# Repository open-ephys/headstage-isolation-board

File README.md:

# headstage-isolation-board

## this design is not functional right now, see below

isolation board for RHD headstge, electrically decouples headstage from aq. board.
This could be useful for mitigating recording noise in some scenarious, or simplify proper grounding practive, especially if multiple recording rigs share the same acquisition board. Eventually, this device could be used to provide safety for human EEG or intracortical applications, but this would require extensive testing and approval procedures.

*This device has not been tested and is not considered safe for any use case. Only use this if you are approved to do so independently.*

# operating principle
This isolation board translates the LVDS signals to a single ended CMOS signal, isolates this signal and translates it back to LVDS. Power isolation is accomplished through a separate 5V isolation transformer.

## 2do:
change this to use the basic design form the FMC card at 
https://github.com/open-ephys/next-gen-system/tree/master/FMC-board

use only IEC60601-1 certified parts, this way we're on the safe side for US and EU standards
http://www.cui.com/catalog/resource/iec-60601-1-medical-design-standards.pdf

power DC-DC: http://www.digikey.com/en/product-highlight/r/recom-power/dcdc-converters
cmos isolation: http://www.analog.com/media/en/technical-documentation/data-sheets/ADuM4400_4401_4402.pdf

# old spec below

Based on Analog Devices ADUM3440 isolators 9 http://www.analog.com/media/en/technical-documentation/data-sheets/ADuM3440_3441_3442.pdf )
UL recognition: 2500 V rms for 1 minute per UL 1577,  CSA Component Acceptance Notice #5A, VDE certificate of conformity, DIN V VDE V 0884-10 (VDE V 0884-10):2006-12 
V_IORM = 560 V peak

LVDS<-> CMOS trsnalation is done via on Analog Devices ADN4664 Dual, 3 V, CMOS, LVDS Differential Line Receivers ( http://www.analog.com/media/en/technical-documentation/data-sheets/ADN4664.pdf ) and ADN4663 Dual, 3 V, CMOS, LVDS High Speed Differential Drivers ( http://www.analog.com/media/en/technical-documentation/data-sheets/ADN4663.pdf )

Power isolation is done with a Murata NMV0505 3kVDC Isolated 5V DC/DC Converters ( http://power.murata.com/data/power/ncl/kdc_nmv.pdf )

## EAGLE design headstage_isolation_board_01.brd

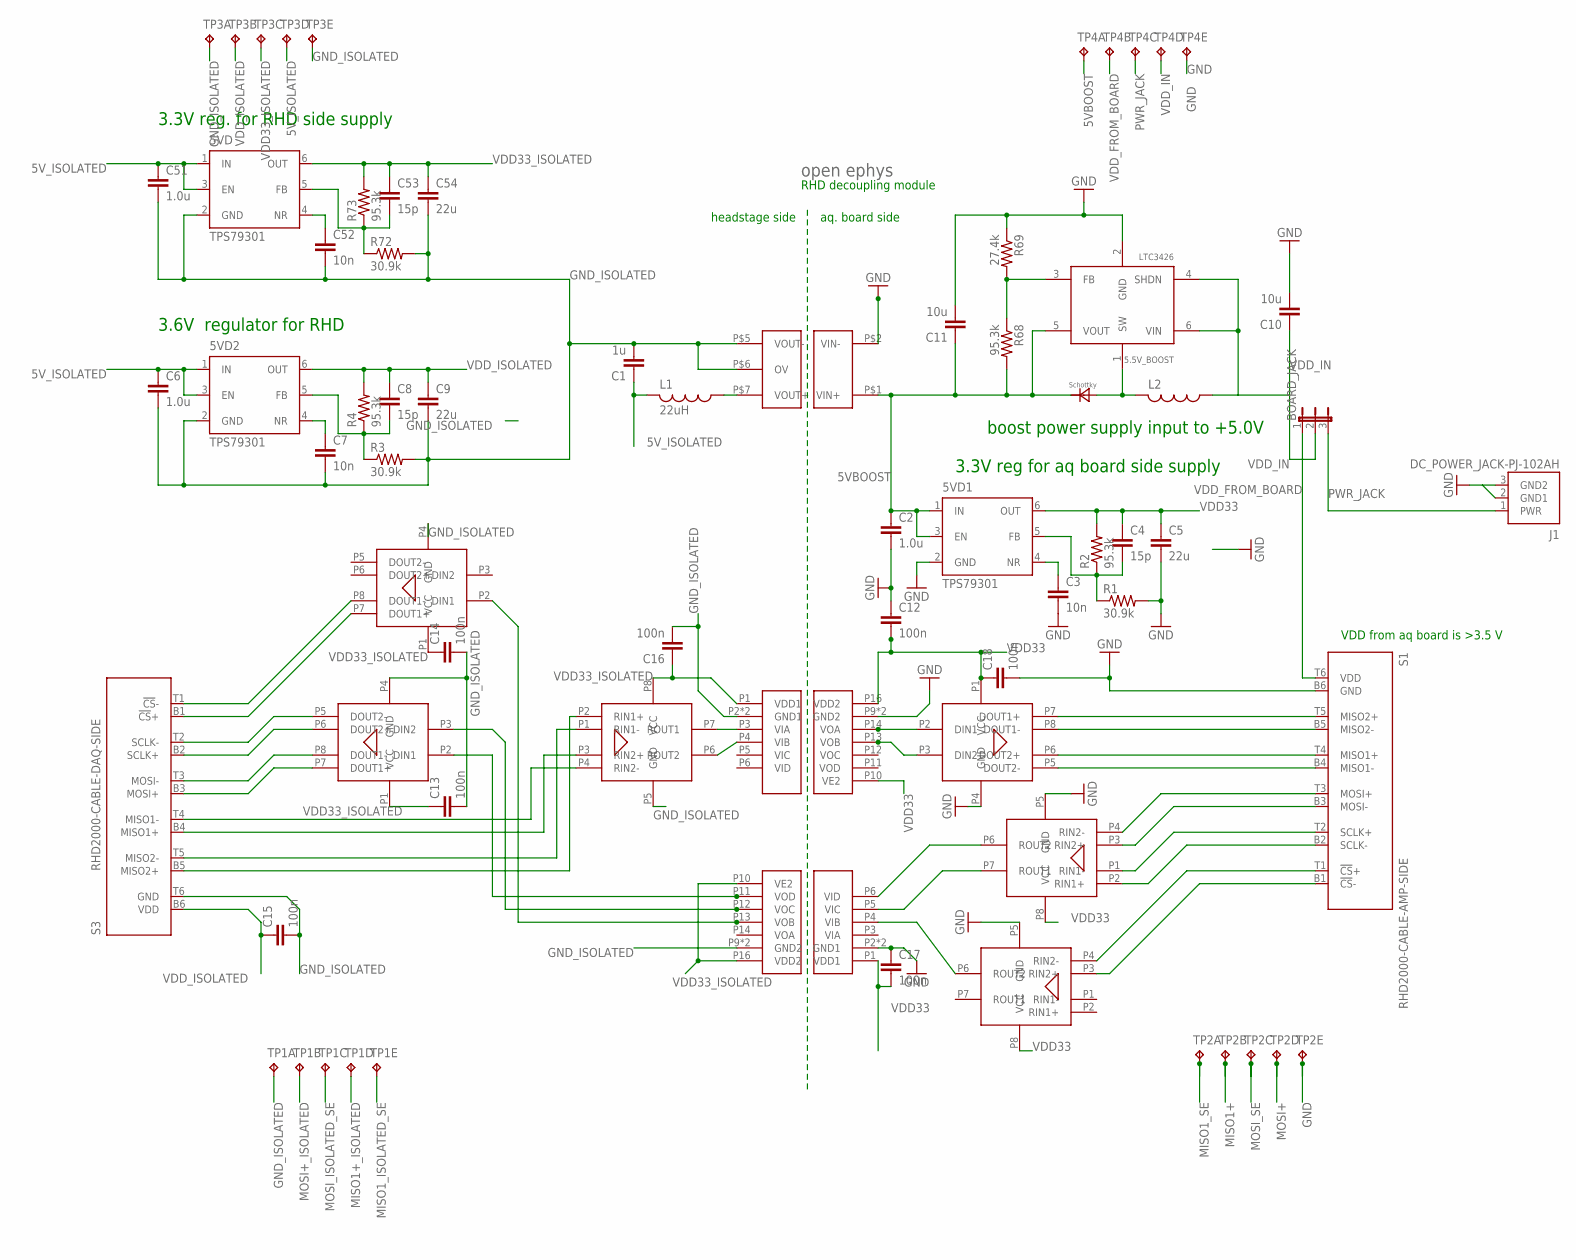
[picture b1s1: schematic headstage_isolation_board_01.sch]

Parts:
5.5V_BOOST: LTC3426; SOT23-6
5VD, 5VD1, 5VD2: TPS79301; SOT-23-6
BOARD_JACK: JP2E; JP2
C1: 1u; 1206
C2, C6, C51: 1.0u; 0805
C3, C7, C52: 10n; 0603
C4, C8, C53: 15p; 0603
C5, C9, C54: 22u; 1206
C10, C11: 10u; 1206
C12, C13, C14, C15, C16, C17, C18: 100n; 0603
D1: MBRA210LT3-D
J1: DC_POWER_JACK-PJ-102AH; PJ-102AH
L1: 22uH; 1206
L2: L_1206; 1206
R1, R3, R72: 30.9k; 0603
R2, R4, R68, R73: 95.3k; 0603
R69: 27.4k; 0603
S1: RHD2000-CABLE-AMP-SIDE; OMNETICS_PZN-12-AA
S3: RHD2000-CABLE-DAQ-SIDE; OMNETICS_PZN-12-AA
TP1, TP2, TP3, TP4: TP5P5-25-13; P5-25-13
U$1: OPEN_EPHYS_LOGO
U$2, U$10: ADUM3440; SOIC_WIDE_16
U$4, U$5, U$9: ADN4663; 8-SOIC
U$6, U$7, U$8: ADN4664; 8-SOIC
U$12: NMV0505

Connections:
5VBOOST: 5.5V_BOOST.5 (VOUT), 5VD1.1 (IN), 5VD1.3 (EN), C2.1, C11.1, D1.NEG, R68.2, TP4.TP-1, U$12.P$1 (VIN+)
5V_ISOLATED: 5VD.1 (IN), 5VD.3 (EN), 5VD2.1 (IN), 5VD2.3 (EN), C1.1, C6.1, C51.1, L1.2, TP3.TP-4
CS+: S1.T1 (!CS!+), U$8.P4 (RIN2-)
CS+_ISOLATED: S3.B1 (!CS!+), U$9.P7 (DOUT1+)
CS-: S1.B1 (!CS!-), U$8.P3 (RIN2+)
CS-_ISOLATED: S3.T1 (!CS!-), U$9.P8 (DOUT1-)
CS_ISOLATED_SE: U$2.P13 (VOB), U$9.P2 (DIN1)
CS_SE: U$2.P4 (VIB), U$8.P6 (ROUT2)
GND: 5.5V_BOOST.2 (GND), 5VD1.2 (GND), C2.2, C3.2, C5.2, C10.2, C11.2, C12.1, C17.1, C18.2, J1.2 (GND1), J1.3 (GND2), R1.2, R69.1, S1.B6 (GND), TP2.TP-5, TP4.TP-5, U$2.P2 (GND1), U$2.P8 (GND1), U$4.P4 (GND), U$7.P5 (GND), U$8.P5 (GND), U$10.P9 (GND2), U$10.P15 (GND2), U$12.P$2 (VIN-)
GND4: C15.2
GND_ISOLATED: 5VD.2 (GND), 5VD2.2 (GND), C1.2, C6.2, C7.2, C9.2, C13.2, C14.2, C16.2, C51.2, C52.2, C54.2, R3.2, R72.2, S3.T6 (GND), TP1.TP-1, TP3.TP-1, TP3.TP-5, U$2.P9 (GND2), U$2.P15 (GND2), U$5.P4 (GND), U$6.P5 (GND), U$9.P4 (GND), U$10.P2 (GND1), U$10.P8 (GND1), U$12.P$5 (VOUT-), U$12.P$6 (OV)
MISO1+: S1.T4 (MISO1+), TP2.TP-2, U$4.P6 (DOUT2+)
MISO1+_ISOLATED: S3.B4 (MISO1+), TP1.TP-4, U$6.P3 (RIN2+); also elsewhere on the board
MISO1-: S1.B4 (MISO1-), U$4.P5 (DOUT2-)
MISO1-_ISOLATED: S3.T4 (MISO1-), U$6.P4 (RIN2-); also elsewhere on the board
MISO1_ISOLATED_SE: TP1.TP-5, U$6.P6 (ROUT2), U$10.P4 (VIB)
MISO1_SE: TP2.TP-1, U$4.P3 (DIN2), U$10.P13 (VOB)
MISO2+: S1.T5 (MISO2+), U$4.P7 (DOUT1+)
MISO2+_ISOLATED: S3.B5 (MISO2+), U$6.P2 (RIN1+); also elsewhere on the board
MISO2-: S1.B5 (MISO2-), U$4.P8 (DOUT1-)
MISO2-_ISOLATED: S3.T5 (MISO2-), U$6.P1 (RIN1-); also elsewhere on the board
MISO2_ISOLATED_SE: U$6.P7 (ROUT1), U$10.P3 (VIA)
MISO2_SE: U$4.P2 (DIN1), U$10.P14 (VOA)
MOSI+: S1.T3 (MOSI+), TP2.TP-4, U$7.P4 (RIN2-)
MOSI+_ISOLATED: S3.B3 (MOSI+), TP1.TP-2, U$5.P7 (DOUT1+)
MOSI-: S1.B3 (MOSI-), U$7.P3 (RIN2+)
MOSI-_ISOLATED: S3.T3 (MOSI-), U$5.P8 (DOUT1-)
MOSI_ISOLATED_SE: TP1.TP-3, U$2.P11 (VOD), U$5.P2 (DIN1)
MOSI_SE: TP2.TP-3, U$2.P6 (VID), U$7.P6 (ROUT2)
unnamed: L1.1, U$12.P$7 (VOUT+)
unnamed: 5VD1.4 (NR), C3.1
unnamed: 5VD1.5 (FB), C4.2, R1.1, R2.1
unnamed: 5VD2.4 (NR), C7.1
unnamed: 5VD2.5 (FB), C8.2, R3.1, R4.1
unnamed: 5VD.4 (NR), C52.1
unnamed: 5VD.5 (FB), C53.2, R72.1, R73.1
unnamed: 5.5V_BOOST.3 (FB), R68.1, R69.2
unnamed: 5.5V_BOOST.1 (SW), D1.POS, L2.2
PWR_JACK: BOARD_JACK.3, J1.1 (PWR), TP4.TP-3
SCLK+: S1.T2 (SCLK+), U$7.P1 (RIN1-)
SCLK+_ISOLATED: S3.B2 (SCLK+), U$5.P6 (DOUT2+)
SCLK-: S1.B2 (SCLK-), U$7.P2 (RIN1+)
SCLK-_ISOLATED: S3.T2 (SCLK-), U$5.P5 (DOUT2-)
SCLK_ISOLATED_SE: U$2.P12 (VOC), U$5.P3 (DIN2)
SCLK_SE: U$2.P5 (VIC), U$7.P7 (ROUT1)
VDD33: 5VD1.6 (OUT), C4.1, C5.1, C12.2, C17.2, C18.1, R2.2, U$2.P1 (VDD1), U$4.P1 (VCC), U$7.P8 (VCC), U$8.P8 (VCC), U$10.P10 (VE2), U$10.P16 (VDD2)
VDD33_ISOLATED: 5VD.6 (OUT), C13.1, C14.1, C16.1, C53.1, C54.1, R73.2, TP3.TP-3, U$2.P10 (VE2), U$2.P16 (VDD2), U$5.P1 (VCC), U$6.P8 (VCC), U$9.P1 (VCC), U$10.P1 (VDD1)
VDD_FROM_BOARD: BOARD_JACK.1, S1.T6 (VDD), TP4.TP-2
VDD_IN: 5.5V_BOOST.4 (SHDN), 5.5V_BOOST.6 (VIN), BOARD_JACK.2, C10.1, L2.1, TP4.TP-4
VDD_ISOLATED: 5VD2.6 (OUT), C8.1, C9.1, C15.1, R4.2, S3.B6 (VDD), TP3.TP-2

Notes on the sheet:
headstage side
aq. board side
VDD from aq board is >3.5 V
RHD decoupling module
boost power supply input to +5.0V
3.3V reg. for RHD side supply
3.3V reg for aq board side supply
3.6V regulator for RHD

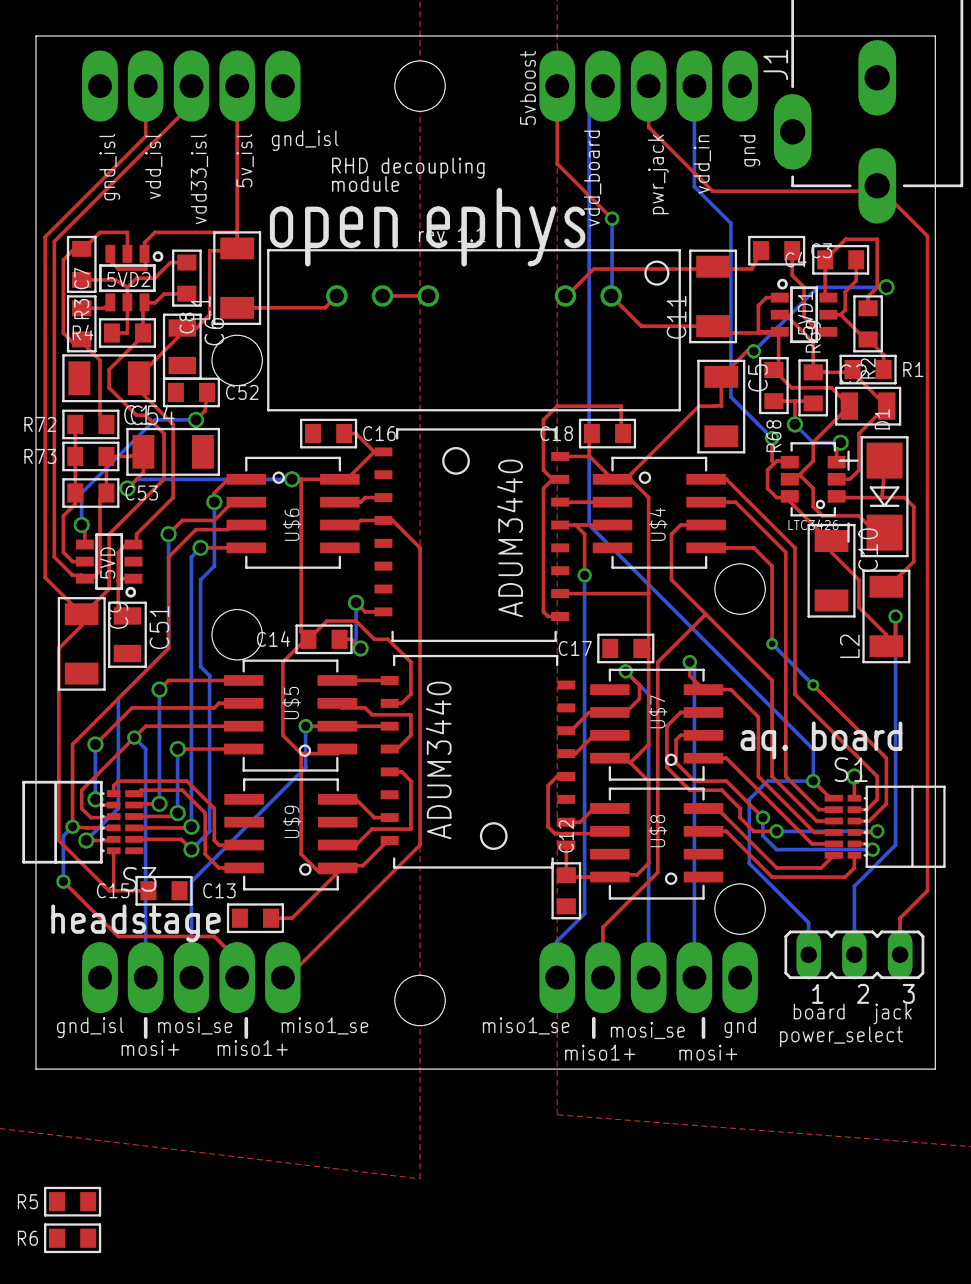
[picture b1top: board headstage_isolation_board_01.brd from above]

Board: 2 copper layers, 50.0 x 57.4 mm, 57 parts (0 on the bottom side), 49 nets.

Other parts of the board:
R5, R6: 100; 0603

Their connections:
MISO1+_ISOLATED: R6.1; also elsewhere on the board
MISO1-_ISOLATED: R6.2; also elsewhere on the board
MISO2+_ISOLATED: R5.1; also elsewhere on the board
MISO2-_ISOLATED: R5.2; also elsewhere on the board

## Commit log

2013-11-19 initial commit
    pretty rough draft, completely lacks DC-DC converter
2013-11-19 added DC-DC converter
    still missing resistors etc
2013-11-19 initial partial layout, added some regulator parts
    still need to change r values for regulators
2013-11-19 more layout of power side
2013-11-19 initial rough layout
    still missing correct resistor values
2013-11-20 routing cleanup, added more bypass caps
2013-12-02 Add gerber files
2013-12-02 Add CAM file and update top silkscreen
2014-08-27 fix some naming CONNECTOR STILL WRONG- DONT USE YET
2014-08-28 added correct connector
2016-02-16 routed correct headstage connector
    and some other fixes.
    Still lacking testpoints
2016-02-16 partially added test points/ dc jack
    can now choose between aq board power and external power jack, and
    added a few test points
2016-02-16 added all test points
2016-02-16 added simple readme
2016-02-19 added LVDS termination resistors
    should fix bug #2
2016-02-19 missing brd updates from last commit
2016-04-07 added 60601-1 2do list
